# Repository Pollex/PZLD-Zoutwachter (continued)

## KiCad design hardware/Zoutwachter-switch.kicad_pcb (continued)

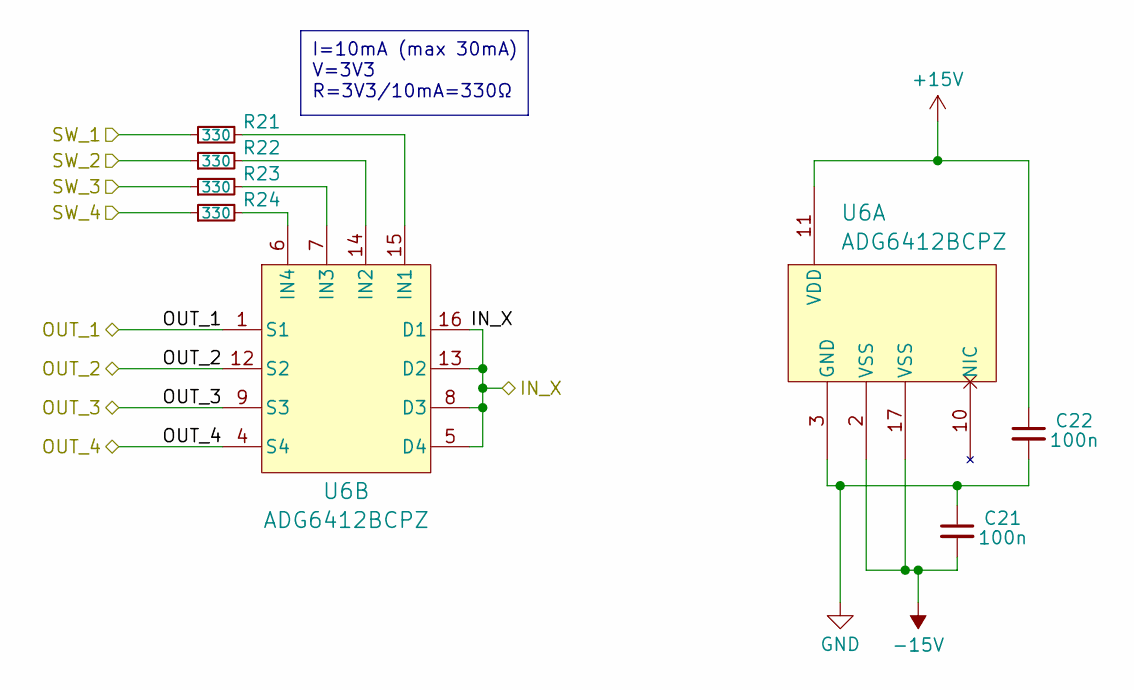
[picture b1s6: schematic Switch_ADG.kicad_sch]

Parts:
C21, C22: 100n; C_0603_1608Metric; LCSC MFR YAGEO
R21, R22, R23, R24: 330; R_0603_1608Metric; LCSC MFR UNI-ROYAL(Uniroyal Elec)
U6: ADG6412BCPZ

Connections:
+15V: C22.1, U6.11 (VDD); also elsewhere on the board
-15V: C21.2, U6.2 (VSS), U6.17 (VSS); also elsewhere on the board
/FIELD_PIN4: U6.5 (D4), U6.8 (D3), U6.13 (D2), U6.16 (D1); also elsewhere on the board
/SENSOR_PIN1: U6.1 (S1); also elsewhere on the board
/SENSOR_PIN2: U6.12 (S2); also elsewhere on the board
/SENSOR_PIN3: U6.9 (S3); also elsewhere on the board
/SENSOR_PIN4: U6.4 (S4); also elsewhere on the board
/Switch_Module1/Switch_ADG1/SW_1: R21.1; also elsewhere on the board
/Switch_Module1/Switch_ADG1/SW_2: R22.1; also elsewhere on the board
/Switch_Module1/Switch_ADG1/SW_3: R23.1; also elsewhere on the board
/Switch_Module1/Switch_ADG1/SW_4: R24.1; also elsewhere on the board
GND: C21.1, C22.2, U6.3 (GND); also elsewhere on the board
unnamed: R21.2, U6.15 (IN1)
unnamed: R22.2, U6.14 (IN2)
unnamed: R23.2, U6.7 (IN3)
unnamed: R24.2, U6.6 (IN4)

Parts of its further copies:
C23, C24, C25, C26, C27, C28, C29, C30, C31, C32, C35, C36, C37, C38, C39, C40, C41, C42, C43, C44, C45, C46, C49, C50, C51, C52, C53, C54, C55, C56, C57, C58, C59, C60, C63, C64, C65, C66, C67, C68, C69, C74, C75, C76, C77, C78: 100n; C_0603_1608Metric; LCSC MFR YAGEO
R25, R26, R27, R28, R29, R30, R31, R32, R33, R34, R35, R36, R37, R38, R39, R40, R41, R42, R43, R44, R45, R46, R47, R48, R49, R50, R51, R52, R53, R54, R55, R56, R57, R58, R59, R60, R61, R62, R63, R64, R65, R66, R67, R68, R69, R70, R71, R72, R73, R74, R75, R76, R77, R78, R79, R80, R81, R82, R83, R84, R85, R86, R87, R88, R89, R90, R91, R92, R93, R94, R95, R96, R97, R98, R99, R100, R101, R102, R103, R104, R105, R106, R107, R108, R109, R110, R111, R112, R113, R114, R115, R116: 330; R_0603_1608Metric; LCSC MFR UNI-ROYAL(Uniroyal Elec)
U7, U8, U9, U10, U11, U15, U16, U17, U18, U19, U20, U21, U22, U23, U24, U25, U26, U27, U28, U29, U30, U31, U32: ADG6412BCPZ

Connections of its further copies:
+15V: C24.1, C26.1, C28.1, C30.1, C32.1, C36.1, C38.1, C40.1, C42.1, C44.1, C46.1, C50.1, C52.1, C54.1, C56.1, C58.1, C60.1, C64.1, C66.1, C68.1, C74.1, C76.1, C78.1, U7.11 (VDD), U8.11 (VDD), U9.11 (VDD), U10.11 (VDD), U11.11 (VDD), U15.11 (VDD), U16.11 (VDD), U17.11 (VDD), U18.11 (VDD), U19.11 (VDD), U20.11 (VDD), U21.11 (VDD), U22.11 (VDD), U23.11 (VDD), U24.11 (VDD), U25.11 (VDD), U26.11 (VDD), U27.11 (VDD), U28.11 (VDD), U29.11 (VDD), U30.11 (VDD), U31.11 (VDD), U32.11 (VDD); also elsewhere on the board
-15V: C23.2, C25.2, C27.2, C29.2, C31.2, C35.2, C37.2, C39.2, C41.2, C43.2, C45.2, C49.2, C51.2, C53.2, C55.2, C57.2, C59.2, C63.2, C65.2, C67.2, C69.2, C75.2, C77.2, U7.2 (VSS), U7.17 (VSS), U8.2 (VSS), U8.17 (VSS), U9.2 (VSS), U9.17 (VSS), U10.2 (VSS), U10.17 (VSS), U11.2 (VSS), U11.17 (VSS), U15.2 (VSS), U15.17 (VSS), U16.2 (VSS), U16.17 (VSS), U17.2 (VSS), U17.17 (VSS), U18.2 (VSS), U18.17 (VSS), U19.2 (VSS), U19.17 (VSS), U20.2 (VSS), U20.17 (VSS), U21.2 (VSS), U21.17 (VSS), U22.2 (VSS), U22.17 (VSS), U23.2 (VSS), U23.17 (VSS), U24.2 (VSS), U24.17 (VSS), U25.2 (VSS), U25.17 (VSS), U26.2 (VSS), U26.17 (VSS), U27.2 (VSS), U27.17 (VSS), U28.2 (VSS), U28.17 (VSS), U29.2 (VSS), U29.17 (VSS), U30.2 (VSS), U30.17 (VSS), U31.2 (VSS), U31.17 (VSS), U32.2 (VSS), U32.17 (VSS); also elsewhere on the board
/FIELD_PIN1: U9.5 (D4), U9.8 (D3), U9.13 (D2), U9.16 (D1); also elsewhere on the board
/FIELD_PIN2: U10.5 (D4), U10.8 (D3), U10.13 (D2), U10.16 (D1); also elsewhere on the board
/FIELD_PIN3: U11.5 (D4), U11.8 (D3), U11.13 (D2), U11.16 (D1); also elsewhere on the board
/FIELD_PIN5: U7.5 (D4), U7.8 (D3), U7.13 (D2), U7.16 (D1); also elsewhere on the board
/FIELD_PIN6: U8.5 (D4), U8.8 (D3), U8.13 (D2), U8.16 (D1); also elsewhere on the board
/FIELD_PIN7: U18.5 (D4), U18.8 (D3), U18.13 (D2), U18.16 (D1); also elsewhere on the board
/FIELD_PIN8: U20.5 (D4), U20.8 (D3), U20.13 (D2), U20.16 (D1); also elsewhere on the board
/FIELD_PIN9: U21.5 (D4), U21.8 (D3), U21.13 (D2), U21.16 (D1); also elsewhere on the board
/FIELD_PIN10: U15.5 (D4), U15.8 (D3), U15.13 (D2), U15.16 (D1); also elsewhere on the board
/FIELD_PIN11: U16.5 (D4), U16.8 (D3), U16.13 (D2), U16.16 (D1); also elsewhere on the board
/FIELD_PIN12: U17.5 (D4), U17.8 (D3), U17.13 (D2), U17.16 (D1); also elsewhere on the board
/FIELD_PIN13: U24.5 (D4), U24.8 (D3), U24.13 (D2), U24.16 (D1); also elsewhere on the board
/FIELD_PIN14: U25.5 (D4), U25.8 (D3), U25.13 (D2), U25.16 (D1); also elsewhere on the board
/FIELD_PIN15: U27.5 (D4), U27.8 (D3), U27.13 (D2), U27.16 (D1); also elsewhere on the board
/FIELD_PIN16: U19.5 (D4), U19.8 (D3), U19.13 (D2), U19.16 (D1); also elsewhere on the board
/FIELD_PIN17: U22.5 (D4), U22.8 (D3), U22.13 (D2), U22.16 (D1); also elsewhere on the board
/FIELD_PIN18: U23.5 (D4), U23.8 (D3), U23.13 (D2), U23.16 (D1); also elsewhere on the board
/FIELD_PIN19: U30.5 (D4), U30.8 (D3), U30.13 (D2), U30.16 (D1); also elsewhere on the board
/FIELD_PIN20: U31.5 (D4), U31.8 (D3), U31.13 (D2), U31.16 (D1); also elsewhere on the board
/FIELD_PIN21: U32.5 (D4), U32.8 (D3), U32.13 (D2), U32.16 (D1); also elsewhere on the board
/FIELD_PIN22: U26.5 (D4), U26.8 (D3), U26.13 (D2), U26.16 (D1); also elsewhere on the board
/FIELD_PIN23: U28.5 (D4), U28.8 (D3), U28.13 (D2), U28.16 (D1); also elsewhere on the board
/FIELD_PIN24: U29.5 (D4), U29.8 (D3), U29.13 (D2), U29.16 (D1); also elsewhere on the board
/SENSOR_PIN1: U7.1 (S1), U8.1 (S1), U9.1 (S1), U10.1 (S1), U11.1 (S1), U15.1 (S1), U16.1 (S1), U17.1 (S1), U18.1 (S1), U19.1 (S1), U20.1 (S1), U21.1 (S1), U22.1 (S1), U23.1 (S1), U24.1 (S1), U25.1 (S1), U26.1 (S1), U27.1 (S1), U28.1 (S1), U29.1 (S1), U30.1 (S1), U31.1 (S1), U32.1 (S1); also elsewhere on the board
/SENSOR_PIN2: U7.12 (S2), U8.12 (S2), U9.12 (S2), U10.12 (S2), U11.12 (S2), U15.12 (S2), U16.12 (S2), U17.12 (S2), U18.12 (S2), U19.12 (S2), U20.12 (S2), U21.12 (S2), U22.12 (S2), U23.12 (S2), U24.12 (S2), U25.12 (S2), U26.12 (S2), U27.12 (S2), U28.12 (S2), U29.12 (S2), U30.12 (S2), U31.12 (S2), U32.12 (S2); also elsewhere on the board
/SENSOR_PIN3: U7.9 (S3), U8.9 (S3), U9.9 (S3), U10.9 (S3), U11.9 (S3), U15.9 (S3), U16.9 (S3), U17.9 (S3), U18.9 (S3), U19.9 (S3), U20.9 (S3), U21.9 (S3), U22.9 (S3), U23.9 (S3), U24.9 (S3), U25.9 (S3), U26.9 (S3), U27.9 (S3), U28.9 (S3), U29.9 (S3), U30.9 (S3), U31.9 (S3), U32.9 (S3); also elsewhere on the board
/SENSOR_PIN4: U7.4 (S4), U8.4 (S4), U9.4 (S4), U10.4 (S4), U11.4 (S4), U15.4 (S4), U16.4 (S4), U17.4 (S4), U18.4 (S4), U19.4 (S4), U20.4 (S4), U21.4 (S4), U22.4 (S4), U23.4 (S4), U24.4 (S4), U25.4 (S4), U26.4 (S4), U27.4 (S4), U28.4 (S4), U29.4 (S4), U30.4 (S4), U31.4 (S4), U32.4 (S4); also elsewhere on the board
/Switch_Module1/Switch_ADG2/SW_1: R25.1; also elsewhere on the board
/Switch_Module1/Switch_ADG2/SW_2: R26.1; also elsewhere on the board
/Switch_Module1/Switch_ADG2/SW_3: R27.1; also elsewhere on the board
/Switch_Module1/Switch_ADG2/SW_4: R28.1; also elsewhere on the board
/Switch_Module1/Switch_ADG3/SW_1: R29.1; also elsewhere on the board
/Switch_Module1/Switch_ADG3/SW_2: R30.1; also elsewhere on the board
/Switch_Module1/Switch_ADG3/SW_3: R31.1; also elsewhere on the board
/Switch_Module1/Switch_ADG3/SW_4: R32.1; also elsewhere on the board
/Switch_Module1/Switch_ADG4/SW_1: R33.1; also elsewhere on the board
/Switch_Module1/Switch_ADG4/SW_2: R34.1; also elsewhere on the board
/Switch_Module1/Switch_ADG4/SW_3: R35.1; also elsewhere on the board
/Switch_Module1/Switch_ADG4/SW_4: R36.1; also elsewhere on the board
/Switch_Module1/Switch_ADG5/SW_1: R37.1; also elsewhere on the board
/Switch_Module1/Switch_ADG5/SW_2: R38.1; also elsewhere on the board
/Switch_Module1/Switch_ADG5/SW_3: R39.1; also elsewhere on the board
/Switch_Module1/Switch_ADG5/SW_4: R40.1; also elsewhere on the board
/Switch_Module1/Switch_ADG6/SW_1: R41.1; also elsewhere on the board
/Switch_Module1/Switch_ADG6/SW_2: R42.1; also elsewhere on the board
/Switch_Module1/Switch_ADG6/SW_3: R43.1; also elsewhere on the board
/Switch_Module1/Switch_ADG6/SW_4: R44.1; also elsewhere on the board
/Switch_Module2/Switch_ADG1/SW_1: R45.1; also elsewhere on the board
/Switch_Module2/Switch_ADG1/SW_2: R46.1; also elsewhere on the board
/Switch_Module2/Switch_ADG1/SW_3: R47.1; also elsewhere on the board
/Switch_Module2/Switch_ADG1/SW_4: R48.1; also elsewhere on the board
/Switch_Module2/Switch_ADG2/SW_1: R49.1; also elsewhere on the board
/Switch_Module2/Switch_ADG2/SW_2: R50.1; also elsewhere on the board
/Switch_Module2/Switch_ADG2/SW_3: R51.1; also elsewhere on the board
/Switch_Module2/Switch_ADG2/SW_4: R52.1; also elsewhere on the board
/Switch_Module2/Switch_ADG3/SW_1: R53.1; also elsewhere on the board
/Switch_Module2/Switch_ADG3/SW_2: R54.1; also elsewhere on the board
/Switch_Module2/Switch_ADG3/SW_3: R55.1; also elsewhere on the board
/Switch_Module2/Switch_ADG3/SW_4: R56.1; also elsewhere on the board
/Switch_Module2/Switch_ADG4/SW_1: R57.1; also elsewhere on the board
/Switch_Module2/Switch_ADG4/SW_2: R58.1; also elsewhere on the board
/Switch_Module2/Switch_ADG4/SW_3: R59.1; also elsewhere on the board
/Switch_Module2/Switch_ADG4/SW_4: R60.1; also elsewhere on the board
/Switch_Module2/Switch_ADG5/SW_1: R61.1; also elsewhere on the board
/Switch_Module2/Switch_ADG5/SW_2: R62.1; also elsewhere on the board
/Switch_Module2/Switch_ADG5/SW_3: R63.1; also elsewhere on the board
/Switch_Module2/Switch_ADG5/SW_4: R64.1; also elsewhere on the board
/Switch_Module2/Switch_ADG6/SW_1: R65.1; also elsewhere on the board
/Switch_Module2/Switch_ADG6/SW_2: R66.1; also elsewhere on the board
/Switch_Module2/Switch_ADG6/SW_3: R67.1; also elsewhere on the board
/Switch_Module2/Switch_ADG6/SW_4: R68.1; also elsewhere on the board
/Switch_Module3/Switch_ADG1/SW_1: R69.1; also elsewhere on the board
/Switch_Module3/Switch_ADG1/SW_2: R70.1; also elsewhere on the board
/Switch_Module3/Switch_ADG1/SW_3: R71.1; also elsewhere on the board
/Switch_Module3/Switch_ADG1/SW_4: R72.1; also elsewhere on the board
/Switch_Module3/Switch_ADG2/SW_1: R73.1; also elsewhere on the board
/Switch_Module3/Switch_ADG2/SW_2: R74.1; also elsewhere on the board
/Switch_Module3/Switch_ADG2/SW_3: R75.1; also elsewhere on the board
/Switch_Module3/Switch_ADG2/SW_4: R76.1; also elsewhere on the board
/Switch_Module3/Switch_ADG3/SW_1: R77.1; also elsewhere on the board
/Switch_Module3/Switch_ADG3/SW_2: R78.1; also elsewhere on the board
/Switch_Module3/Switch_ADG3/SW_3: R79.1; also elsewhere on the board
/Switch_Module3/Switch_ADG3/SW_4: R80.1; also elsewhere on the board
/Switch_Module3/Switch_ADG4/SW_1: R81.1; also elsewhere on the board
/Switch_Module3/Switch_ADG4/SW_2: R82.1; also elsewhere on the board
/Switch_Module3/Switch_ADG4/SW_3: R83.1; also elsewhere on the board
/Switch_Module3/Switch_ADG4/SW_4: R84.1; also elsewhere on the board
/Switch_Module3/Switch_ADG5/SW_1: R85.1; also elsewhere on the board
/Switch_Module3/Switch_ADG5/SW_2: R86.1; also elsewhere on the board
/Switch_Module3/Switch_ADG5/SW_3: R87.1; also elsewhere on the board
/Switch_Module3/Switch_ADG5/SW_4: R88.1; also elsewhere on the board
/Switch_Module3/Switch_ADG6/SW_1: R89.1; also elsewhere on the board
/Switch_Module3/Switch_ADG6/SW_2: R90.1; also elsewhere on the board
/Switch_Module3/Switch_ADG6/SW_3: R91.1; also elsewhere on the board
/Switch_Module3/Switch_ADG6/SW_4: R92.1; also elsewhere on the board
/Switch_Module4/Switch_ADG1/SW_1: R93.1; also elsewhere on the board
/Switch_Module4/Switch_ADG1/SW_2: R94.1; also elsewhere on the board
/Switch_Module4/Switch_ADG1/SW_3: R95.1; also elsewhere on the board
/Switch_Module4/Switch_ADG1/SW_4: R96.1; also elsewhere on the board
/Switch_Module4/Switch_ADG2/SW_1: R97.1; also elsewhere on the board
/Switch_Module4/Switch_ADG2/SW_2: R98.1; also elsewhere on the board
/Switch_Module4/Switch_ADG2/SW_3: R99.1; also elsewhere on the board
/Switch_Module4/Switch_ADG2/SW_4: R100.1; also elsewhere on the board
/Switch_Module4/Switch_ADG3/SW_1: R101.1; also elsewhere on the board
/Switch_Module4/Switch_ADG3/SW_2: R102.1; also elsewhere on the board
/Switch_Module4/Switch_ADG3/SW_3: R103.1; also elsewhere on the board
/Switch_Module4/Switch_ADG3/SW_4: R104.1; also elsewhere on the board
/Switch_Module4/Switch_ADG4/SW_1: R105.1; also elsewhere on the board
/Switch_Module4/Switch_ADG4/SW_2: R106.1; also elsewhere on the board
/Switch_Module4/Switch_ADG4/SW_3: R107.1; also elsewhere on the board
/Switch_Module4/Switch_ADG4/SW_4: R108.1; also elsewhere on the board
/Switch_Module4/Switch_ADG5/SW_1: R109.1; also elsewhere on the board
/Switch_Module4/Switch_ADG5/SW_2: R110.1; also elsewhere on the board
/Switch_Module4/Switch_ADG5/SW_3: R111.1; also elsewhere on the board
/Switch_Module4/Switch_ADG5/SW_4: R112.1; also elsewhere on the board
/Switch_Module4/Switch_ADG6/SW_1: R113.1; also elsewhere on the board
/Switch_Module4/Switch_ADG6/SW_2: R114.1; also elsewhere on the board
/Switch_Module4/Switch_ADG6/SW_3: R115.1; also elsewhere on the board
/Switch_Module4/Switch_ADG6/SW_4: R116.1; also elsewhere on the board
GND: C23.1, C24.2, C25.1, C26.2, C27.1, C28.2, C29.1, C30.2, C31.1, C32.2, C35.1, C36.2, C37.1, C38.2, C39.1, C40.2, C41.1, C42.2, C43.1, C44.2, C45.1, C46.2, C49.1, C50.2, C51.1, C52.2, C53.1, C54.2, C55.1, C56.2, C57.1, C58.2, C59.1, C60.2, C63.1, C64.2, C65.1, C66.2, C67.1, C68.2, C69.1, C74.2, C75.1, C76.2, C77.1, C78.2, U7.3 (GND), U8.3 (GND), U9.3 (GND), U10.3 (GND), U11.3 (GND), U15.3 (GND), U16.3 (GND), U17.3 (GND), U18.3 (GND), U19.3 (GND), U20.3 (GND), U21.3 (GND), U22.3 (GND), U23.3 (GND), U24.3 (GND), U25.3 (GND), U26.3 (GND), U27.3 (GND), U28.3 (GND), U29.3 (GND), U30.3 (GND), U31.3 (GND), U32.3 (GND); also elsewhere on the board
unnamed: R25.2, U7.15 (IN1)
unnamed: R26.2, U7.14 (IN2)
unnamed: R27.2, U7.7 (IN3)
unnamed: R28.2, U7.6 (IN4)
unnamed: R29.2, U8.15 (IN1)
unnamed: R30.2, U8.14 (IN2)
unnamed: R31.2, U8.7 (IN3)
unnamed: R32.2, U8.6 (IN4)
unnamed: R33.2, U9.15 (IN1)
unnamed: R34.2, U9.14 (IN2)
unnamed: R35.2, U9.7 (IN3)
unnamed: R36.2, U9.6 (IN4)
unnamed: R37.2, U10.15 (IN1)
unnamed: R38.2, U10.14 (IN2)
unnamed: R39.2, U10.7 (IN3)
unnamed: R40.2, U10.6 (IN4)
unnamed: R41.2, U11.15 (IN1)
unnamed: R42.2, U11.14 (IN2)
unnamed: R43.2, U11.7 (IN3)
unnamed: R44.2, U11.6 (IN4)
unnamed: R45.2, U15.15 (IN1)
unnamed: R46.2, U15.14 (IN2)
unnamed: R47.2, U15.7 (IN3)
unnamed: R48.2, U15.6 (IN4)
unnamed: R49.2, U16.15 (IN1)
unnamed: R50.2, U16.14 (IN2)
unnamed: R51.2, U16.7 (IN3)
unnamed: R52.2, U16.6 (IN4)
unnamed: R53.2, U17.15 (IN1)
unnamed: R54.2, U17.14 (IN2)
unnamed: R55.2, U17.7 (IN3)
unnamed: R56.2, U17.6 (IN4)
unnamed: R57.2, U18.15 (IN1)
unnamed: R58.2, U18.14 (IN2)
unnamed: R59.2, U18.7 (IN3)
unnamed: R60.2, U18.6 (IN4)
unnamed: R69.2, U19.15 (IN1)
unnamed: R70.2, U19.14 (IN2)
unnamed: R71.2, U19.7 (IN3)
unnamed: R72.2, U19.6 (IN4)
unnamed: R61.2, U20.15 (IN1)
unnamed: R62.2, U20.14 (IN2)
unnamed: R63.2, U20.7 (IN3)
unnamed: R64.2, U20.6 (IN4)
unnamed: R65.2, U21.15 (IN1)
unnamed: R66.2, U21.14 (IN2)
unnamed: R67.2, U21.7 (IN3)
unnamed: R68.2, U21.6 (IN4)
unnamed: R73.2, U22.15 (IN1)
unnamed: R74.2, U22.14 (IN2)
unnamed: R75.2, U22.7 (IN3)
unnamed: R76.2, U22.6 (IN4)
unnamed: R77.2, U23.15 (IN1)
unnamed: R78.2, U23.14 (IN2)
unnamed: R79.2, U23.7 (IN3)
unnamed: R80.2, U23.6 (IN4)
unnamed: R81.2, U24.15 (IN1)
unnamed: R82.2, U24.14 (IN2)
unnamed: R83.2, U24.7 (IN3)
unnamed: R84.2, U24.6 (IN4)
unnamed: R85.2, U25.15 (IN1)
unnamed: R86.2, U25.14 (IN2)
unnamed: R87.2, U25.7 (IN3)
unnamed: R88.2, U25.6 (IN4)
unnamed: R93.2, U26.15 (IN1)
unnamed: R94.2, U26.14 (IN2)
unnamed: R95.2, U26.7 (IN3)
unnamed: R96.2, U26.6 (IN4)
unnamed: R89.2, U27.15 (IN1)
unnamed: R90.2, U27.14 (IN2)
unnamed: R91.2, U27.7 (IN3)
unnamed: R92.2, U27.6 (IN4)
unnamed: R97.2, U28.15 (IN1)
unnamed: R98.2, U28.14 (IN2)
unnamed: R99.2, U28.7 (IN3)
unnamed: R100.2, U28.6 (IN4)
unnamed: R101.2, U29.15 (IN1)
unnamed: R102.2, U29.14 (IN2)
unnamed: R103.2, U29.7 (IN3)
unnamed: R104.2, U29.6 (IN4)
unnamed: R105.2, U30.15 (IN1)
unnamed: R106.2, U30.14 (IN2)
unnamed: R107.2, U30.7 (IN3)
unnamed: R108.2, U30.6 (IN4)
unnamed: R109.2, U31.15 (IN1)
unnamed: R110.2, U31.14 (IN2)
unnamed: R111.2, U31.7 (IN3)
unnamed: R112.2, U31.6 (IN4)
unnamed: R113.2, U32.15 (IN1)
unnamed: R114.2, U32.14 (IN2)
unnamed: R115.2, U32.7 (IN3)
unnamed: R116.2, U32.6 (IN4)

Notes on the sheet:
I=10mA (max 30mA) V=3V3 R=3V3/10mA=330Ω

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
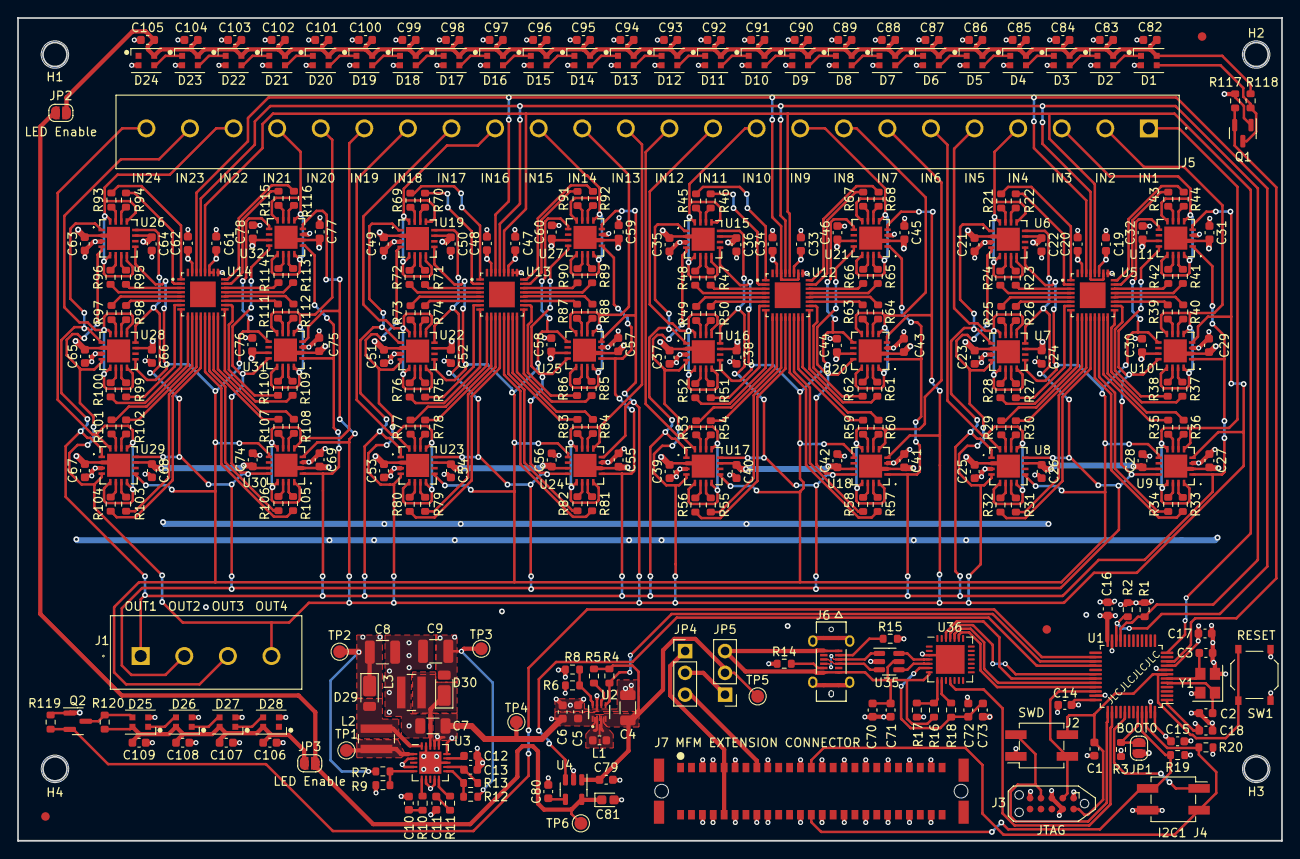
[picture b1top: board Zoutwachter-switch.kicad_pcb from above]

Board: 4 copper layers, 147.3 x 95.9 mm, 325 parts (0 on the bottom side), 306 nets.

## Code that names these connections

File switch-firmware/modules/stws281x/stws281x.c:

#include "stws281x.h"
#include "stm32l071xx.h"

#define LED_L_CCR 13
#define LED_H_CCR 26

#define LED_COUNT 24
#define LED_IDLE_COUNT 120
#define LED_BUFFER_SIZE 24 * LED_COUNT
uint8_t led_buffer_total[LED_BUFFER_SIZE + LED_IDLE_COUNT] = {0};
uint8_t *led_buffer = led_buffer_total + LED_IDLE_COUNT;

void stws281x_init(void) {
    // Setup DMA
    // CxS = 1000
    // TIM2_CH1 on CH5
    //
    // ADDR in DMA_CPARx or DMA_CMARx in circular mode
    // DMA_CNDTRx = total number of data to transfer
    // DMA_CCRx for configuration
    //  - direction (1 = MEM2PER)
    //      DMAR for memory
    //      DPAR for periph
    //  - circular
    //  - other stuff
    // Activate with ENABLE bit in DMA_CCRx
    // DMA Interrupts on TCIFx TCIEx = transfer complete channel X

    RCC->AHBENR |= RCC_AHBENR_DMA1EN;
    DMA1_CSELR->CSELR |= 0b1000 << DMA_CSELR_C5S_Pos;
    DMA1_Channel5->CPAR = (uint32_t)(&TIM2->CCR1);
    // Periph is 32bit, Source is 8 bit
    DMA1_Channel5->CCR |= DMA_CCR_PSIZE_1 //| DMA_CCR_MSIZE_1 // WORD (32 bits)
                          | DMA_CCR_MINC  // Increment memory addr
                          | DMA_CCR_DIR;  //
                                          //| DMA_CCR_CIRC; //
                                          //| DMA_CCR_TCIE  //
    // DMA1_Channel5->CCR |= DMA_CCR_EN;

    // 32 MHz
    // Period  = 1.25us
    // Duty lo = 33%
    // Duty hi = 66%
    //
    // Fpwm = FCLK / (ARR+1) * (PSC+1))
    // 800kHz = 32MHz / (39 * 1)
    //
    // Duty lo = 33% = 13
    // Duty hi = 66% = 26
    //
    // PB13 = LED_OUT = TIM21_CH1
    // PA0 = LED_IN = TIM2_CH1

    // ====
    // TIM2
    // ====
    GPIOA->MODER |= GPIO_MODER_MODE0_1;
    GPIOA->MODER &= ~GPIO_MODER_MODE0_0;
    GPIOA->AFR[0] |= 2 << 0; // Set AF2 for Pin 0
    GPIOA->OSPEEDR |= GPIO_OSPEEDER_OSPEED0_1 | GPIO_OSPEEDER_OSPEED0_0;

    RCC->APB1ENR |= RCC_APB1ENR_TIM2EN;

    TIM2->PSC = 0;
    TIM2->ARR = 39;
    TIM2->CCR1 = 0;

    TIM2->CCMR1 |= TIM_CCMR1_OC1M_2 | TIM_CCMR1_OC1M_1 | TIM_CCMR1_OC1PE;
    TIM2->CCER |= TIM_CCER_CC1E; // CC1E Capture/Compare 1 output Enable
    TIM2->EGR = TIM_EGR_UG; // Set UG bit to trigger shadow register transfer
    TIM2->DIER = TIM_DIER_CC1DE;
    TIM2->CR1 = TIM_CR1_ARPE;
    //|TIM_CR1_CEN     // CEN Counter ENable
    //
    for (int ix = 0; ix < LED_BUFFER_SIZE; ix++)
        led_buffer[ix] = LED_L_CCR;
}

void stws281x_clearall(void) {
    for (int ix = 0; ix < LED_BUFFER_SIZE; ix++)
        led_buffer[ix] = LED_L_CCR;
}

void stws281x_set(uint8_t n, uint8_t R, uint8_t G, uint8_t B) {
    uint8_t *ptr = &led_buffer[n * 24];
    for (int ix = 0; ix < 8; ix++) {
        if (G & 0x80)
            *ptr++ = LED_H_CCR;
        else 
            *ptr++ = LED_L_CCR;
        G <<= 1;
    }
    for (int ix = 0; ix < 8; ix++) {
        if (R & 0x80)
            *ptr++ = LED_H_CCR;
        else 
            *ptr++ = LED_L_CCR;
        R <<= 1;
    }
    for (int ix = 0; ix < 8; ix++) {
        if (B & 0x80)
            *ptr++ = LED_H_CCR;
        else 
            *ptr++ = LED_L_CCR;
        B <<= 1;
    }
}

void stws281x_clear(uint8_t n) {
    uint8_t *ptr = &led_buffer[n * 24];
    for (int i = 0; i < 24; i++) {
        *ptr++ = LED_L_CCR;
    }
}

void stws281x_write(void) {
    // Reload configuration
    DMA1_CSELR->CSELR |= 0b1000 << DMA_CSELR_C5S_Pos;
    // Periph is 32bit, Source is 8 bit
    DMA1_Channel5->CCR |= DMA_CCR_PSIZE_1 //| DMA_CCR_MSIZE_1 // WORD (32 bits)
                          | DMA_CCR_MINC  // Increment memory addr
                          | DMA_CCR_DIR;  //
    DMA1_Channel5->CMAR = (uint32_t)led_buffer_total;
    DMA1_Channel5->CNDTR = LED_BUFFER_SIZE + LED_IDLE_COUNT;
    DMA1_Channel5->CPAR = (uint32_t)(&TIM2->CCR1);

    // Enable
    TIM2->CCR1 = 0;
    TIM2->CR1 |= TIM_CR1_CEN; // CEN Counter ENable
    DMA1_Channel5->CCR |= DMA_CCR_EN;

    // Wait till finished
    while ((DMA1->ISR & (DMA_ISR_TCIF5 | DMA_ISR_TEIF5)) == 0);

    // Disable TIMER  + DMA
    TIM2->CR1 &= ~TIM_CR1_CEN; 
    DMA1_Channel5->CCR &= ~DMA_CCR_EN;
    // Clear flags
    DMA1->IFCR = DMA_IFCR_CTEIF5 | DMA_IFCR_CTCIF5;
}

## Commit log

2024-01-05 SBC: add config, swap serial port pkg
2024-03-29 Update board.h for newest proto
2024-03-29 feat(RGB): WS2812B driver
2024-03-29 Change main.c to switch on first PCAL.
2024-04-02 Refactor(ws2812b): Move to module
2024-04-03 fix(ws281x): off by 1 and desync
2024-04-10 Refactor API's
2024-04-10 Fix pcal bug wrong pin set
2024-04-12 Add elektrode switch and CSV write
2024-04-12 feat(sbc): Configurable cn0359 baud/addr
2024-04-15 feat(sbc): add stabilization time after switch
2024-04-15 fix(switch): update all elektrodes at once
2024-04-16 refactor(sbc): new config, multiple go files
2025-06-18 Update sbc-software
2025-06-18 diagram add kelvin circuit-ish
2025-06-18 commit pending hw changes (rather old by now...)
2025-06-18 FW: update pins
2025-06-18 rename switch-firmware folder
2025-06-18 HW: update to latest version
2025-06-18 refactor(fw): separate files, add openocd.cfg, add FAT
2025-06-18 chore(fw): update tasks in readme
